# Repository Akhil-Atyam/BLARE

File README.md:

# Hotwheel alarm clock!
Hello guys, welcome to my BLARE project!!!
AI DISCLAMER: AI was used in order to understand code, teach classes, and do a bit of struct work. C++ is not my forte, I code in java. I tried to use my own skills as much as possible but I am new so I had to use AI in order to utilize advanced concepts. 

I decided to do this project because one, its a cool mission, two, rest in peace insignia google home alarm clock, you served me well for 8 years.
In essence, my old alarm clock got bricked by google, and I needed a new one.

## What was my thought process? 
Well, at first I just build a run of the mill alarm clock from the tutorial, but as per regulations and also because I was bored i decided to make something unique.
As a kid, i really wanted a hot wheel garage, honestly still do. So I decided to make a hot wheel alarm clock!

## The Design
I based it off the tutorial at first, then used a DXF file i found to etch the logo into the cad. Any AMS printer should be able to handle this.
I also added a phone stand, this way i can maybe add a magsafe puck later and also use my phones standby mode.

## The PCB
This pcb is very similar to the tutorial, my apologies i just quite literally suck at PCB design. 
BUTTT, I did add something, a grounding plane! I realize my traces were going to be tight, and I learned how to make one from a previous project.
This way, i use WAYYY less traces.

## The code
C++ is not my language, im trying to learn, but its hard.
My main goal was to try and create 3 modes, like my CASIO watch!!!
In essence, it has a mode menu, where u can create and store up to 10 alarms (my watch can only do one so major upgrade)
AI was used in order to help me as i barely know c++

## BOM
* 4x Cherry MX Switches
* 1x XIAO ESP32-C3
* 4x Blank DSA Keycaps
* 4x M3x16 Bolt
* 4x M3 Heatset

### Pictures
Top case:

Bottom case: 

Schematic:

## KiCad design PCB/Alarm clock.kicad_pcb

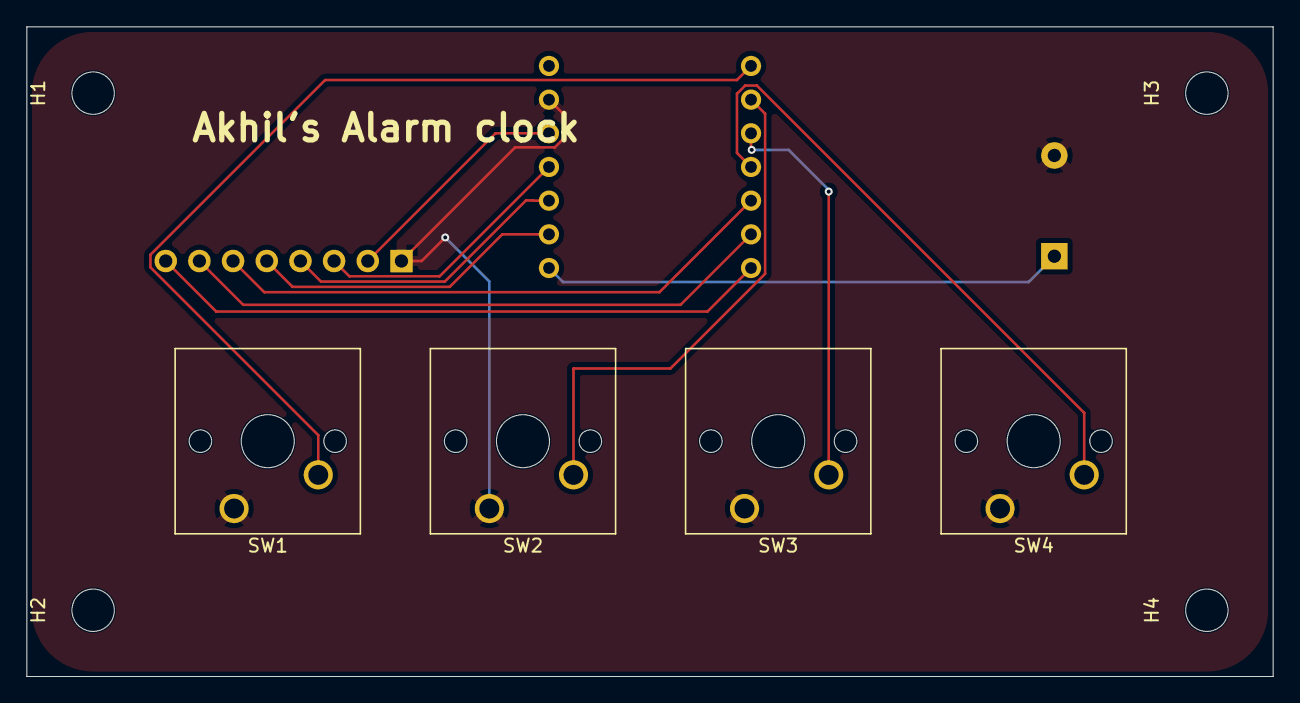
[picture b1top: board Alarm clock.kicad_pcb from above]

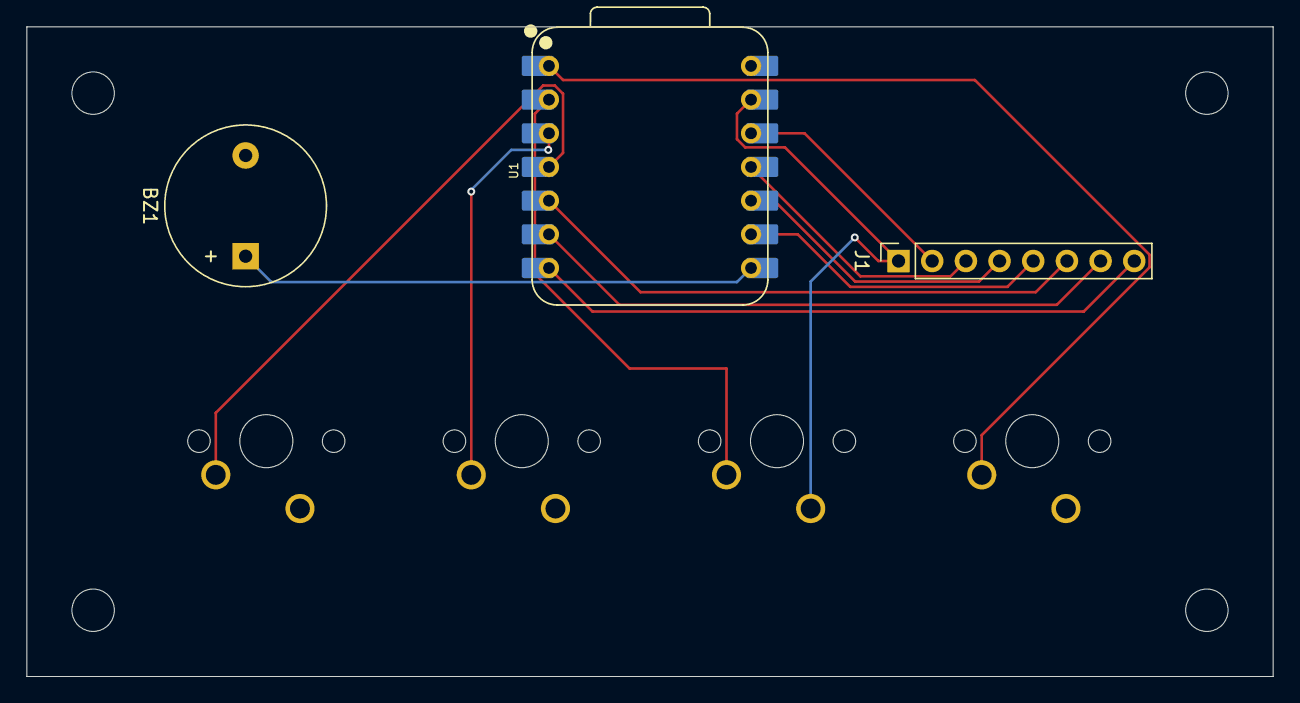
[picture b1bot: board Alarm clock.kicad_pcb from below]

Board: 2 copper layers, 94.0 x 49.0 mm, 11 parts (3 on the bottom side), 13 nets.

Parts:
BZ1: Buzzer; Buzzer_12x9.5RM7.6
H1, H2, H3, H4: MountingHole; MountingHole_3.2mm_M3
J1: Conn_01x08_Pin; PinSocket_1x08_P2.54mm_Vertical
SW1, SW2, SW3, SW4: SW_Push; SW_Cherry_MX_1.00u_PCB
U1: XIAO-ESP32-C3-SMD; XIAO-ESP32-C3-DIP

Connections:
+3V3: J1.2, U1.12 (3V3_OUT)
/BL: J1.8, U1.7 (D6)
/CS: J1.7, U1.6 (D5)
/DC: J1.6, U1.5 (D4)
/RST: J1.5, U1.9 (D8)
/SCL: J1.4, U1.10 (D9/BOOT)
/SDA: J1.3, U1.11 (D10)
GND: BZ1.2 (-), J1.1, SW1.1, SW2.1, SW3.1, SW4.1, U1.13 (GND)
unnamed: BZ1.1 (+), U1.8 (D7)
unnamed: SW1.2, U1.1 (D0)
unnamed: SW2.2, U1.2 (D1)
unnamed: SW3.2, U1.3 (D2)
unnamed: SW4.2, U1.4 (D3)
